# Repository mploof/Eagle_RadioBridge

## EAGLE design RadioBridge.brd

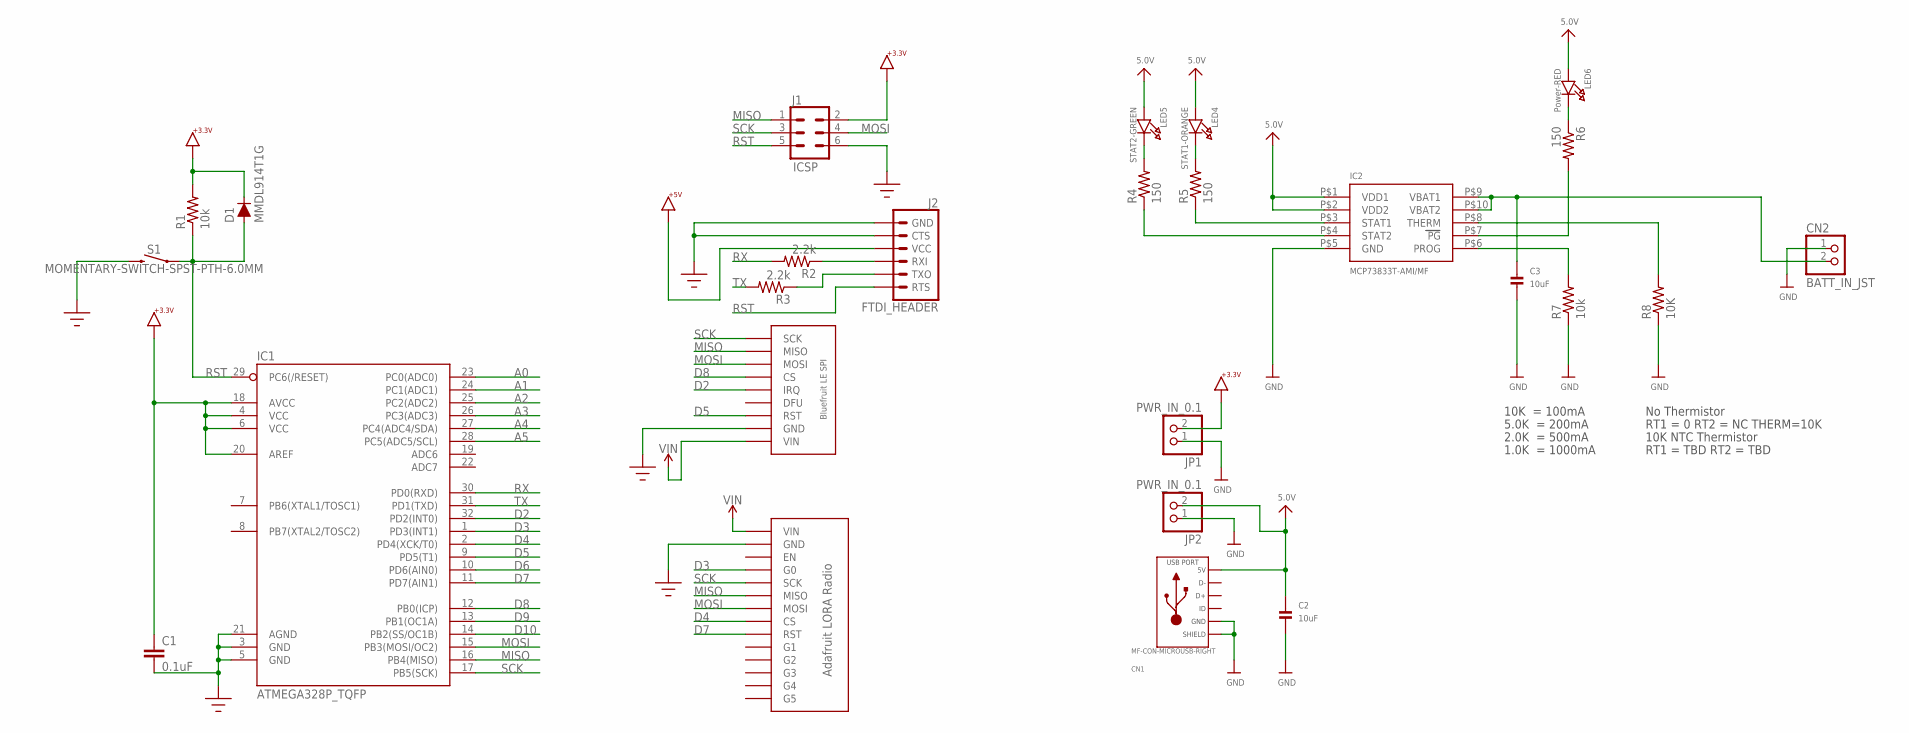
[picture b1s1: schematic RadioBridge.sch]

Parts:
C1: 0.1uF; 0603
C2, C3: 10uF; 0805
CN1: MF-CON-MICROUSB-RIGHT; MICROUSB-RIGHT
CN2: BATT_IN_JST; JSTPH2
D1: MMDL914T1G; SOD-323
IC1: ATMEGA328P_TQFP; TQFP32-08
IC2: MCP73833T-AMI/MF; DFN10_3X3MM
J1: ICSP; 2X3
J2: FTDI_HEADER; 1X06_LOCK
JP1, JP2: PWR_IN_0.1; 1X02_OVAL
LED4: STAT1-ORANGE; CHIPLED_0805
LED5: STAT2-GREEN; CHIPLED_0805
LED6: Power-RED; CHIPLED_0805
R1, R7: 10k; 0603-RES
R2, R3: 2.2k; 0603-RES
R4, R5, R6: 150; 0603-RES
R8: 10K; 0603-RES
S1: MOMENTARY-SWITCH-SPST-PTH-6.0MM; TACTILE_SWITCH_PTH_6.0MM
U$1: BLUEFRUIT_LE_FRIEND_SPI
U$2: ADAFRUIT_LORA_RADIO

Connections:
5.0V: C2.1, CN1.1 (5V), IC2.P$1 (VDD1), IC2.P$2 (VDD2), JP2.2, LED4.A, LED5.A, LED6.A
+3.3V: C1.1, D1.C, IC1.4 (VCC), IC1.6 (VCC), IC1.18 (AVCC), IC1.20 (AREF), J1.2, JP1.2, R1.2
+5V: J2.4 (VCC)
A0: IC1.23 (PC0(ADC0))
A1: IC1.24 (PC1(ADC1))
A2: IC1.25 (PC2(ADC2))
A3: IC1.26 (PC3(ADC3))
A4: IC1.27 (PC4(ADC4/SDA))
A5: IC1.28 (PC5(ADC5/SCL))
BATT1: C3.1, CN2.2, IC2.P$9 (VBAT1), IC2.P$10 (VBAT2)
D2: IC1.32 (PD2(INT0)), U$1.P$5 (IRQ)
D3: IC1.1 (PD3(INT1)), U$2.P$4 (G0)
D4: IC1.2 (PD4(XCK/T0)), U$2.P$8 (CS)
D5: IC1.9 (PD5(T1)), U$1.P$7 (RST)
D6: IC1.10 (PD6(AIN0))
D7: IC1.11 (PD7(AIN1)), U$2.P$9 (RST)
D8: IC1.12 (PB0(ICP)), U$1.P$4 (CS)
D9: IC1.13 (PB1(OC1A))
D10: IC1.14 (PB2(SS/OC1B))
GND: C1.2, C2.2, C3.2, CN1.5 (GND), CN1.S1 (SLD), CN1.S2 (SLD), CN1.S3 (SLD), CN1.S4 (SLD), CN1.S5 (SLD), CN1.S6 (SLD), CN2.1, IC1.3 (GND), IC1.5 (GND), IC1.21 (AGND), IC2.P$5 (GND), J1.6, J2.5 (CTS), J2.6 (GND), JP1.1, JP2.1, R7.1, R8.1, S1.3 (2), U$1.P$8 (GND), U$2.P$2 (GND)
MISO: IC1.16 (PB4(MISO)), J1.1, U$1.P$2 (MISO), U$2.P$6 (MISO)
MOSI: IC1.15 (PB3(MOSI/OC2)), J1.4, U$1.P$3 (MOSI), U$2.P$7 (MOSI)
unnamed: LED4.C, R5.2
unnamed: LED5.C, R4.2
unnamed: IC2.P$3 (STAT1), R5.1
unnamed: IC2.P$4 (STAT2), R4.1
unnamed: LED6.C, R6.1
unnamed: IC2.P$6 (PROG), R7.2
unnamed: IC2.P$7 (PG), R6.2
unnamed: IC2.P$8 (THERM), R8.2
RST: D1.A, IC1.29 (PC6(/RESET)), J1.5, J2.1 (RTS), R1.1, S1.1
RX: IC1.30 (PD0(RXD)), R2.2
RXI: J2.3 (RXI), R2.1
SCK: IC1.17 (PB5(SCK)), J1.3, U$1.P$1 (SCK), U$2.P$5 (SCK)
TX: IC1.31 (PD1(TXD)), R3.2
TXO: J2.2 (TXO), R3.1
VIN: U$1.P$9 (VIN), U$2.P$1 (VIN)

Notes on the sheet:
10K = 100mA
5.0K = 200mA
2.0K = 500mA
1.0K = 1000mA
No Thermistor
RT1 = 0 RT2 = NC THERM=10K
10K NTC Thermistor
RT1 = TBD RT2 = TBD

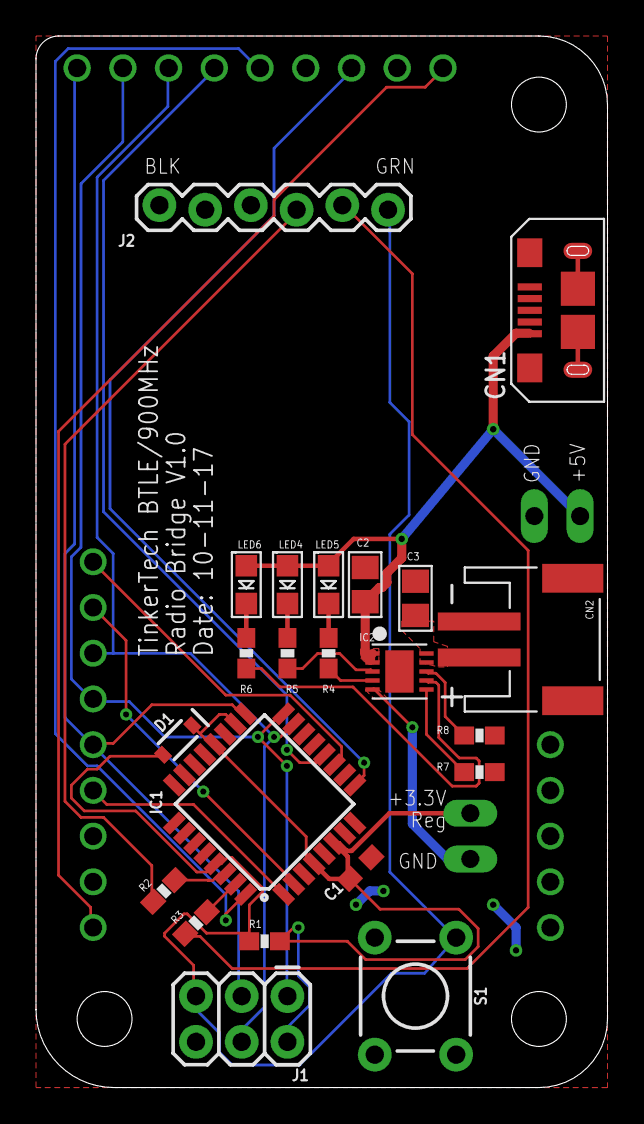
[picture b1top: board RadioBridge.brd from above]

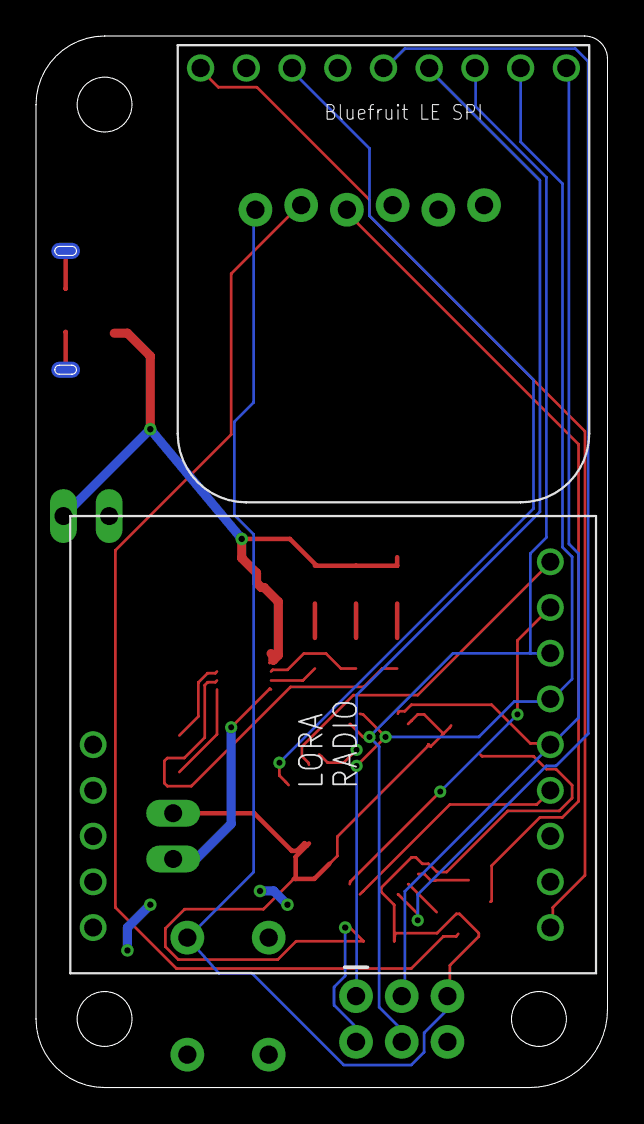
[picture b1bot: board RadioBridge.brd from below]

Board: 2 copper layers, 31.7 x 58.4 mm, 26 parts (2 on the bottom side), 27 nets.

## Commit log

2017-10-01 Set Eagle .gitignore
2017-10-01 In progress
2017-10-12 Completed V1.0 circuit

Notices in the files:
parts and their libraries:
SparkFun-IC-Microcontroller: Licensing: Creative Commons ShareAlike 4.0 International - https://creativecommons.org/licenses/by-sa/4.0
SparkFun-Passives: Licensing: CC v3.0 Share-Alike You are welcome to use this library for commercial purposes.
